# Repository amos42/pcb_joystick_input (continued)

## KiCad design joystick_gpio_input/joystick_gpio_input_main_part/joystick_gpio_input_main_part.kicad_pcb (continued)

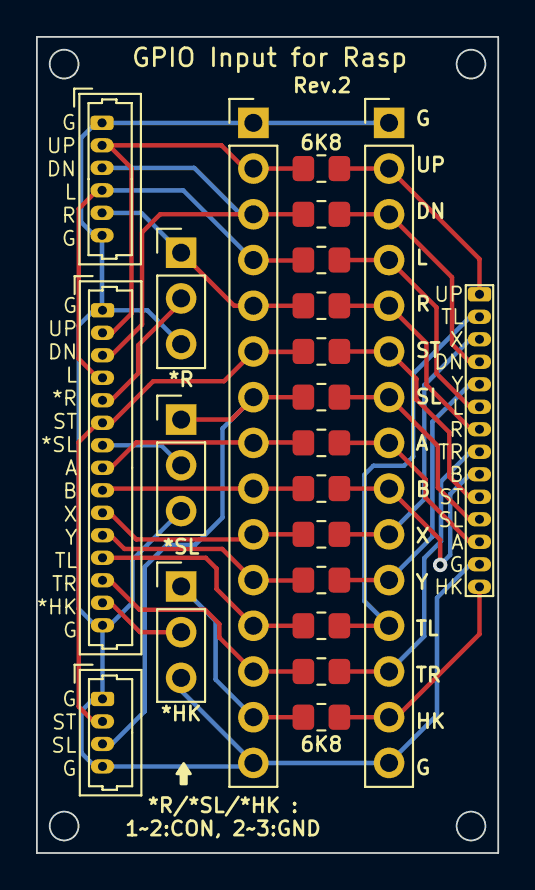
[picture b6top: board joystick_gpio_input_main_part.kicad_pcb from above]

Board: 2 copper layers, 25.6 x 45.3 mm, 22 parts (0 on the bottom side), 30 nets.

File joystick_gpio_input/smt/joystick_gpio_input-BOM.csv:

Designator,Footprint,Comment
"R10,R12,R13,R11,R4,R9,R5,R2,R8,R3,R7,R6,R1",R_0805_2012Metric_Pad1.20x1.40mm_HandSolder,6K8

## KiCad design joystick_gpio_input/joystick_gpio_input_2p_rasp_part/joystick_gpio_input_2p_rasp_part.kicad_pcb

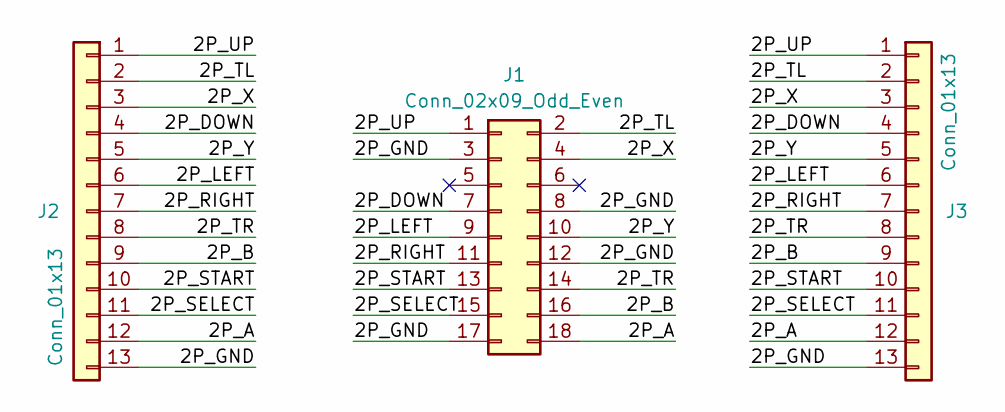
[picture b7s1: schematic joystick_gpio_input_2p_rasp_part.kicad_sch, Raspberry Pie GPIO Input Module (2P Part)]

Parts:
J1: Conn_02x09_Odd_Even; PinSocket_2x09_P2.54mm_Vertical
J2: Conn_01x13; conn_ex_1x13_P1.25mm_Vertical_Right_Labeled
J3: Conn_01x13; conn_ex_1x13_P1.25mm_Vertical_Left_Labeled

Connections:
/2P_A: J1.18, J2.12, J3.12
/2P_B: J1.16, J2.9, J3.9
/2P_DOWN: J1.7, J2.4, J3.4
/2P_GND: J1.3, J1.8, J1.12, J1.17, J2.13, J3.13
/2P_LEFT: J1.9, J2.6, J3.6
/2P_RIGHT: J1.11, J2.7, J3.7
/2P_SELECT: J1.15, J2.11, J3.11
/2P_START: J1.13, J2.10, J3.10
/2P_TL: J1.2, J2.2, J3.2
/2P_TR: J1.14, J2.8, J3.8
/2P_UP: J1.1, J2.1, J3.1
/2P_X: J1.4, J2.3, J3.3
/2P_Y: J1.10, J2.5, J3.5

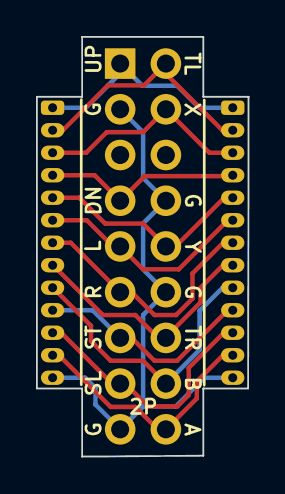
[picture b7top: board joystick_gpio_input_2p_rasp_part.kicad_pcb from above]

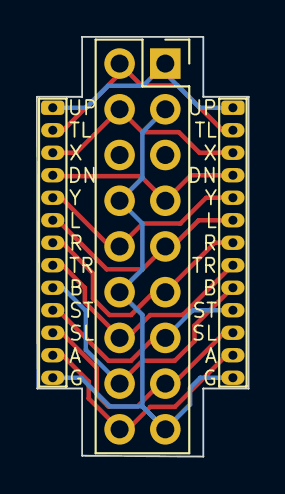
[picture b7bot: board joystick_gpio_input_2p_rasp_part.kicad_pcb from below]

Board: 2 copper layers, 11.8 x 23.3 mm, 3 parts (3 on the bottom side), 13 nets.

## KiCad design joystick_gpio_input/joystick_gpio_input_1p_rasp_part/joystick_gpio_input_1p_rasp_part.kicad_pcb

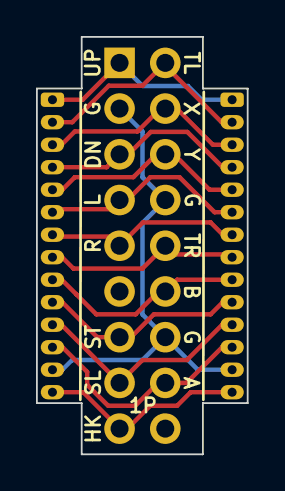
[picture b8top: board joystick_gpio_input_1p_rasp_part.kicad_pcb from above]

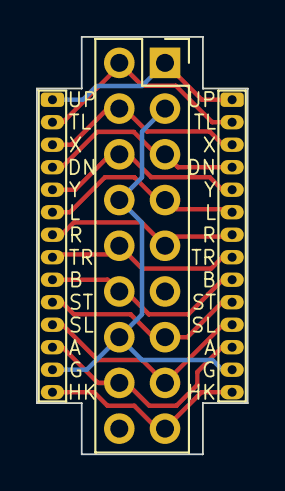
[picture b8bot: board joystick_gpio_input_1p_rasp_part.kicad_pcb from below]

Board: 2 copper layers, 11.7 x 23.2 mm, 3 parts (3 on the bottom side), 14 nets.

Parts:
J1: Conn_02x09_Odd_Even; PinSocket_2x09_P2.54mm_Vertical
J2: Conn_01x14; conn_ex_1x14_P1.25mm_Vertical_Right_Labeled
J3: Conn_01x14; conn_ex_1x14_P1.25mm_Vertical_Left_Labeled

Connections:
/1P_A: J1.16, J2.12, J3.12
/1P_B: J1.12, J2.9, J3.9
/1P_DOWN: J1.5, J2.4, J3.4
/1P_GND: J1.3, J1.8, J1.14, J2.13, J3.13
/1P_HK: J1.17, J2.14, J3.14
/1P_LEFT: J1.7, J2.6, J3.6
/1P_RIGHT: J1.9, J2.7, J3.7
/1P_SELECT: J1.15, J2.11, J3.11
/1P_START: J1.13, J2.10, J3.10
/1P_TL: J1.2, J2.2, J3.2
/1P_TR: J1.10, J2.8, J3.8
/1P_UP: J1.1, J2.1, J3.1
/1P_X: J1.4, J2.3, J3.3
/1P_Y: J1.6, J2.5, J3.5

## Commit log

2023-02-12 부품 값 입력
2023-02-12 gpio 입력 보드 점퍼 변경
2023-02-12 gpio input 보드 크기 조정
2023-02-13 gpio 입력 보드 확장
2023-03-11 gpio 입력 보드 커넥터 1개씩 늘림
2023-03-26 Rev 2 설계
2023-04-01 gpio 입력 보드 개별로 분리
2023-04-01 gpio 입력 보드 미세 조정
2023-04-02 joystick gpio 스크린샷 추가
2023-04-02 이미지 링크 교체
2023-04-02 gpio 보드 나사 구멍 미세 조정
2023-05-21 입력 드라이버 주소 마킹
2023-12-06 gpio 입력시 1p용 핀맵 이미지 추가
2023-12-08 arcade 입력 패널 supoort 보드 추가
2023-12-10 배선 최적화 및 레이아웃 변경
2023-12-11 이미지 변경
2023-12-11 문서 보강 (pcb 이미지 추가)
2023-12-22 커넥터 추가
2023-12-28 입력 패널 버튼 서포터 rev 2
2023-12-28 위치 조정
2024-01-01 입력 패널 보조 이미지 파일 변경
2024-01-01 입력 패널 서포트 문서 파일 보강
2024-01-01 입력 패널 서포터 보조 이미지 보완
2024-01-01 입력 패널 서포터 이미지 변경
